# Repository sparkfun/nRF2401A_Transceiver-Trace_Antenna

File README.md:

nRF2401A Transceiver- Trace Antenna
==================================
[  
*nRF2401A Transceiver with Trace Antenna (WRL-00153)*](https://github.com/sparkfun/nRF2401A_Transceiver-Trace_Antenna)

This is a breakout board for the nRF2401A 2.4GHz transceiver module with a built-in trace antenna. 

Repository Contents
-------------------
* **/Firmware** - Example firmware to use with the chip
* **/Hardware** - All Eagle design files (.brd, .sch)

License Information
-------------------
The hardware is released under [Creative Commons Share-alike 3.0](http://creativecommons.org/licenses/by-sa/3.0/).  
All other code is open source so please feel free to do anything you want with it; 
you buy me a beer if you use this and we meet someday ([Beerware license](http://en.wikipedia.org/wiki/Beerware)).

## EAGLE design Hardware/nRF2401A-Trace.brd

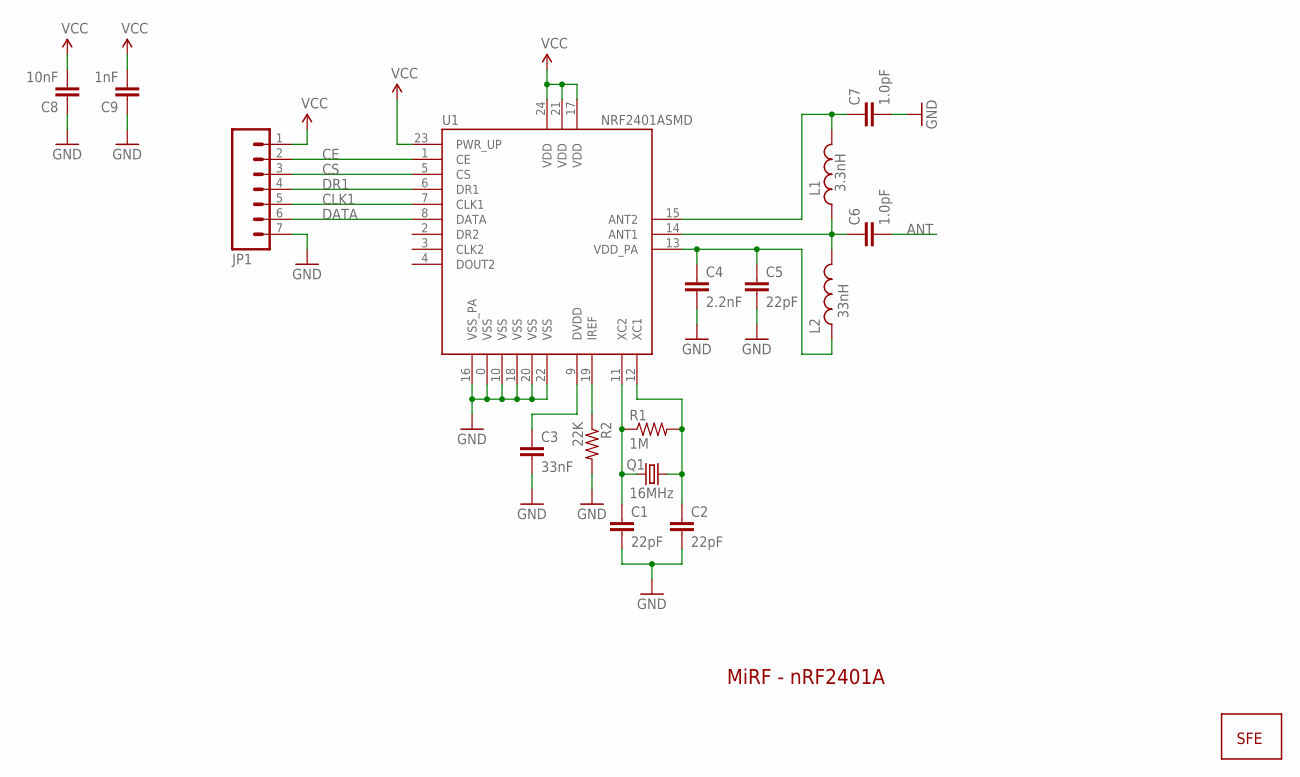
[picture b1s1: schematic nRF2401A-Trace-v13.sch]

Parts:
C1, C2, C5: 22pF; 0402-CAP
C3: 33nF; 0402-CAP
C4: 2.2nF; 0402-CAP
C6, C7: 1.0pF; 0402-CAP
C8: 10nF; 0402-CAP
C9: 1nF; 0402-CAP
JP1: M07; 1X07
L1: 3.3nH; C0402
L2: 33nH; C0402
Q1: 16MHz; CRYSTAL-SMD-5X3
R1: 1M; 0402-RES
R2: 22K; 0402-RES
U1: NRF2401ASMD; MLP-24
U$1: LOGO-SFESK; SFE-LOGO-FLAME

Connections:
ANT: C6.2
CE: JP1.2, U1.1 (CE)
CLK1: JP1.5, U1.7 (CLK1)
CS: JP1.3, U1.5 (CS)
DATA: JP1.6, U1.8 (DATA)
DR1: JP1.4, U1.6 (DR1)
GND: C1.2, C2.2, C3.2, C4.2, C5.2, C7.2, C8.1, C9.1, JP1.7, R2.2, U1.0 (VSS), U1.10 (VSS), U1.16 (VSS_PA), U1.18 (VSS), U1.20 (VSS), U1.22 (VSS)
unnamed: C1.1, Q1.1, R1.1, U1.11 (XC2)
unnamed: C2.1, Q1.3 (2), R1.2, U1.12 (XC1)
unnamed: C6.1, L1.1, L2.2, U1.14 (ANT1)
unnamed: R2.1, U1.19 (IREF)
unnamed: C3.1, U1.9 (DVDD)
unnamed: C7.1, L1.2, U1.15 (ANT2)
unnamed: C4.1, C5.1, L2.1, U1.13 (VDD_PA)
VCC: C8.2, C9.2, JP1.1, U1.17 (VDD), U1.21 (VDD), U1.23 (PWR_UP), U1.24 (VDD)

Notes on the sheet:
MiRF - nRF2401A

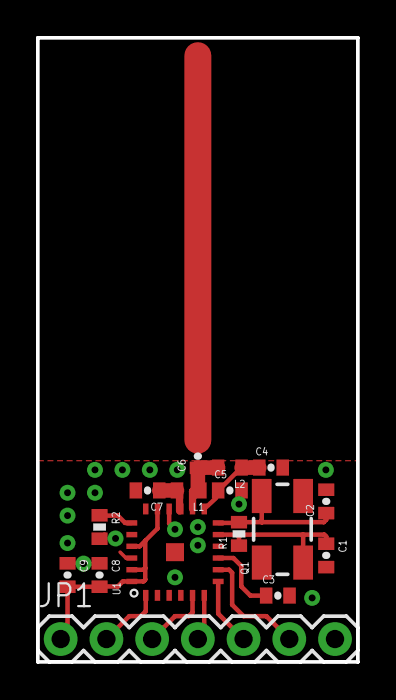
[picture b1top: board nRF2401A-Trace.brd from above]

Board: 2 copper layers, 17.8 x 34.7 mm, 17 parts (1 on the bottom side), 14 nets.

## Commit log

2013-09-04 Initial file commit
2013-10-08 Adding .brd file to Hardware
